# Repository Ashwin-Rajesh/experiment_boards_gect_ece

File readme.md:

# Working models

---

# Index
- [Working models](#working-models)
- [Index](#index)
- [Projects](#projects)
- [KiCad](#kicad)
  - [Introduction](#introduction)
  - [KiCad design flow](#kicad-design-flow)
    - [Creating the project](#creating-the-project)
    - [In eschema](#in-eschema)
    - [In PCBnew](#in-pcbnew)
    - [Other points](#other-points)
    - [Layout layers](#layout-layers)
  - [Design standards for the boards](#design-standards-for-the-boards)

---

# Projects

1) Series voltage regulator with feedback

---

# KiCad

## Introduction

KiCad is used for all schematic and board design. First, each board has a separate project. KiCad projects have 4 types of files 
- ```.pro```
  - Stores project related information
- ```.lib```
  - Libraries
- ```.sch```
  - Schematic file
  - Opened using ```Eeschema```
- ```.kicad_pcb```
  - PCB layout file
  - Opened using ```PCBnew```
- ```.net```
  - Netlist file
- ```.gbr```
  - Gerber files
  - Files used to define layers for fabrication
  - Opened using ```gerbview```

Software that are part of KiCad
- ```Eeschema```
  - Schematic editor and viewer
  - File extension : ```.sch```
- ```PCBnew```
  - Layout editor and viewer
  - File extension : ```.kicad_pcb```
- ```Gerbview```
  - Viewer for gerber files
  - File extension : ```.grbjob```

---

## KiCad design flow

### Creating the project
1) Create a project using ```File``` -> ```New``` -> ```Project```. 

### In eschema

1) Click on the ```.sch``` file to open schematic in eeschema
2) Draw the layout
    - Add components using ```Place symbol``` on the right pane or shortcut ```A```
    - Connect them using wires (Right pane : ```Place wire```, shortcut ```W```)
    - Place labels (Right pane : ```Place net label```, ```Place global label```)
    - Add text and stuff if you need it
3) Run ```Annotate schematic symbols``` on the top.
4) Perform DRC using ```Perform design rules check``` on the top.
5) Assign footprints to the symbols we have added using ```Assign PCB footprints to schematic symbols``` in the top.
6) Generate netlist using ```generate netlist``` button on the top.
7) Open PCBnew using ```run PCBnew to layout printed circuit board```

### In PCBnew

1) Run ```Update PCB from schematic``` to import the required footprints from the previous step
2) Arrange the components
     - Move using ```M```
     - Add filled zones using ```Add filled zones``` in the right pane
     - Add wires using ```Route tracks``` in the right pane 
       - Choose required layer in ```layers``` tab in right pane
       - If the layers tab is not visible, check ```show/hide layers manager toolbar```
     - Right click filled zones and ```fill``` to generate gaps
3) Add text and lines and stuff for layers
4) Define board outline using polygons or lines on the ```Edge.cuts``` layer

### Other points

- You can navigate easily between PCBnew and eeschema using buttons on the top
- Everytime you make a change in the schematic, it needs to be updated in the PCB. 
  - Run ```Update PCB from schematic``` in ```PCBnew``` when this is needed 
  - Change options as required
  - No need to generate netlist everytime

### Layout layers

- ```F.Cu``` : Front copper
- ```B.Cu``` : Back copper
- ```F.Silks``` : Front silkscreen
- ```B.Silks``` : Back silkscreen
- ```Edge.cuts``` : Edges of the PCB

---

## Design standards for the boards

- Height must be ```78mm```
- Length maximum ```155mm```
- Use connectors for ```2.54mm```

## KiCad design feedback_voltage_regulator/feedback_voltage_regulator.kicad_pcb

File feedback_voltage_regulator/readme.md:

# Feedback controlled voltage regulator

Linear series voltage regulator with feedback.

---

### Schematic

---

### PCB layout

Dimensions : ```135mm x 78mm```

---

### Gerber file 

---

### 3D view

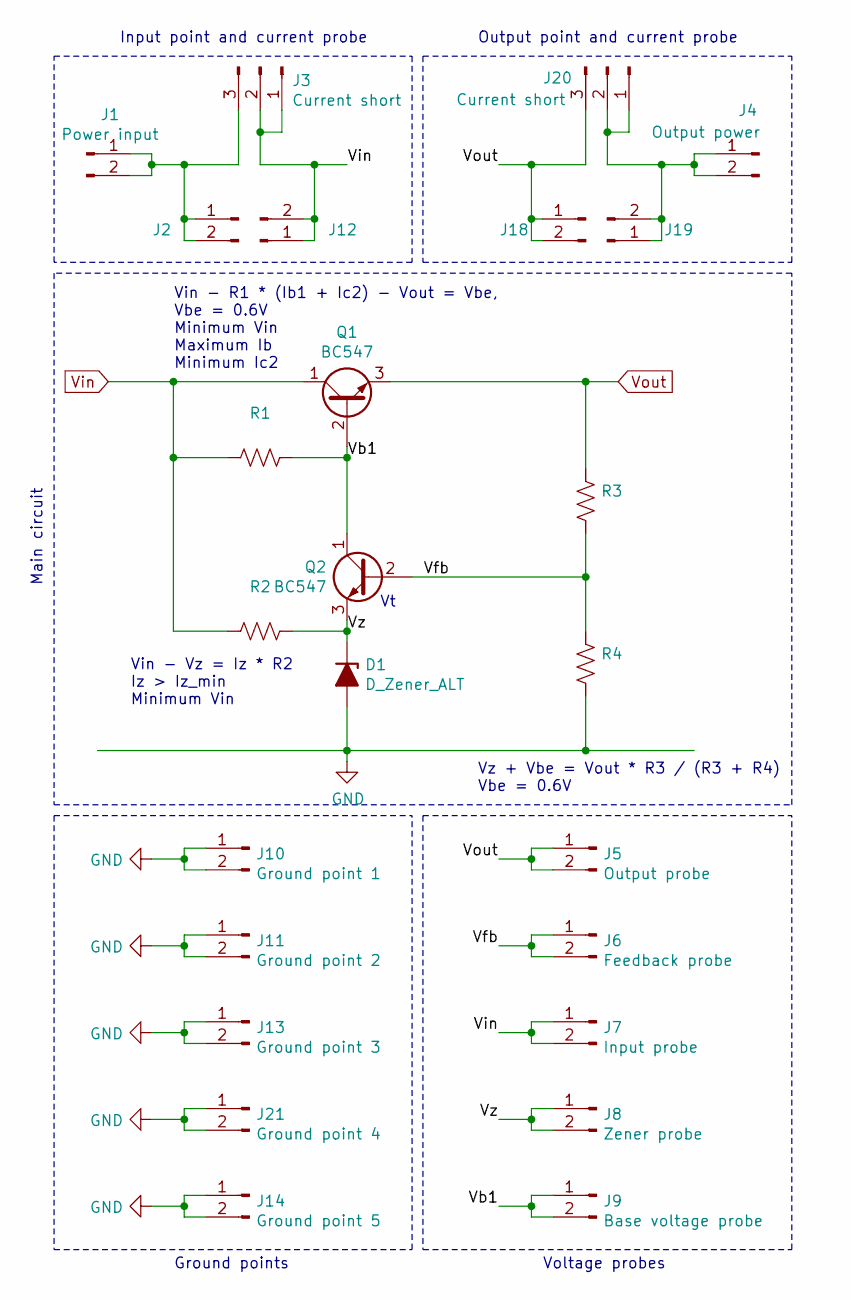
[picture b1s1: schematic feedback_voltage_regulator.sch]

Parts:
D1: D_Zener_ALT; D_DO-15_P15.24mm_Horizontal
J1: Power input; PinHeader_1x02_P2.54mm_Vertical
J2, J12, J18, J19: Input current probe; PinHeader_1x02_P2.54mm_Vertical
J3, J20: Current short; PinHeader_1x03_P2.54mm_Vertical
J4: Output power; PinHeader_1x02_P2.54mm_Vertical
J5: Output probe; PinHeader_1x02_P2.54mm_Vertical
J6: Feedback probe; PinHeader_1x02_P2.54mm_Vertical
J7: Input probe; PinHeader_1x02_P2.54mm_Vertical
J8: Zener probe; PinHeader_1x02_P2.54mm_Vertical
J9: Base voltage probe; PinHeader_1x02_P2.54mm_Vertical
J10: Ground point 1; PinHeader_1x02_P2.54mm_Vertical
J11: Ground point 2; PinHeader_1x02_P2.54mm_Vertical
J13: Ground point 3; PinHeader_1x02_P2.54mm_Vertical
J14: Ground point 5; PinHeader_1x02_P2.54mm_Vertical
J21: Ground point 4; PinHeader_1x02_P2.54mm_Vertical
Q1, Q2: BC547; TO-39-3
R1, R2, R3, R4: R_US; R_Axial_DIN0309_L9.0mm_D3.2mm_P15.24mm_Horizontal

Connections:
/Vb1: J9.1, J9.2, Q1.2 (B), Q2.1 (C), R1.1
/Vfb: J6.1, J6.2, Q2.2 (B), R3.2, R4.1
/Vz: D1.1 (K), J8.1, J8.2, Q2.3 (E), R2.1
GND: D1.2 (A), J10.1, J10.2, J11.1, J11.2, J13.1, J13.2, J14.1, J14.2, J21.1, J21.2, R4.2
unnamed: J1.1, J1.2, J2.1, J2.2, J3.3
unnamed: J4.1, J4.2, J19.1, J19.2, J20.1, J20.2
Vin: J3.1, J3.2, J7.1, J7.2, J12.1, J12.2, Q1.1 (C), R1.2, R2.2
Vout: J5.1, J5.2, J18.1, J18.2, J20.3, Q1.3 (E), R3.1

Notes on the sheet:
Vin - R1 * (Ib1 + Ic2) - Vout = Vbe, Vbe = 0.6V Minimum Vin Maximum Ib Minimum Ic2
Vin - Vz = Iz * R2 Iz > Iz_min Minimum Vin
Vz + Vbe = Vout * R3 / (R3 + R4) Vbe = 0.6V
Voltage probes
Ground points
Output point and current probe
Input point and current probe
Main circuit

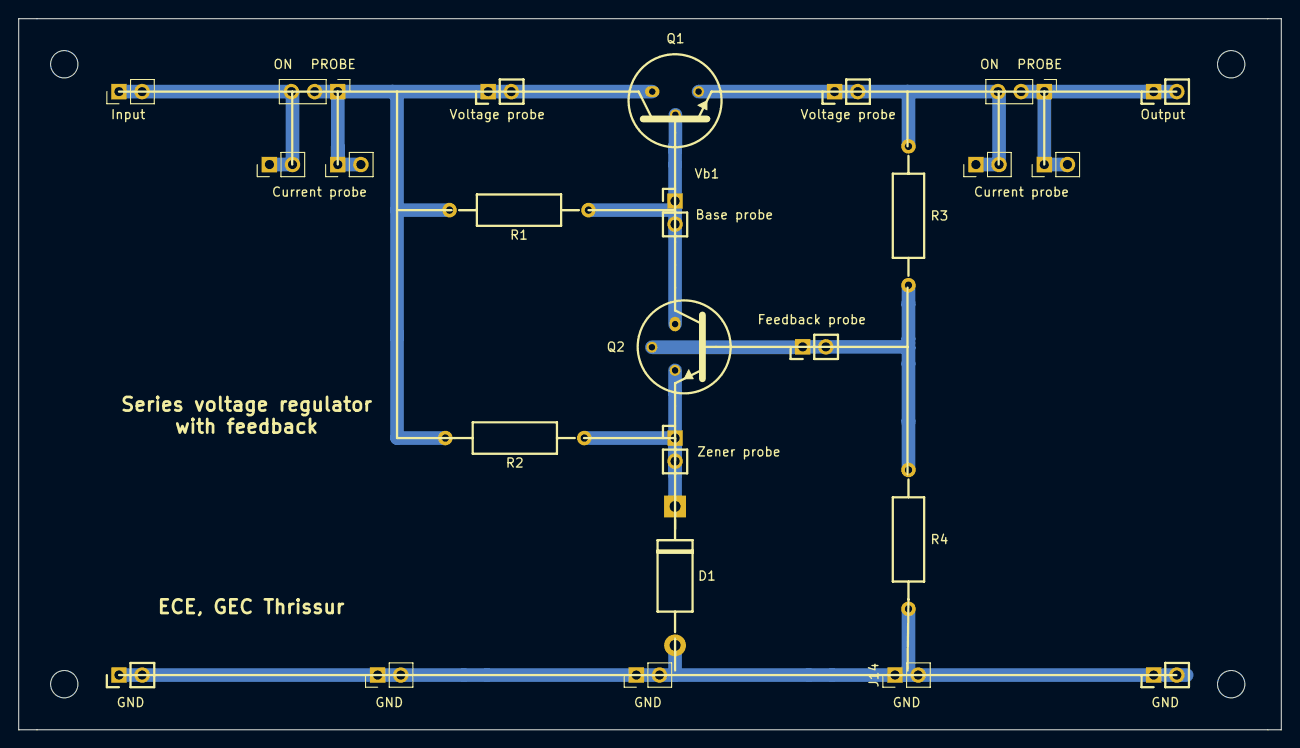
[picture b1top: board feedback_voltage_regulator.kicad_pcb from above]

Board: 2 copper layers, 138.5 x 78.0 mm, 25 parts (0 on the bottom side), 8 nets.

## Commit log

2021-11-26 Added feedback voltage regulator
2021-11-26 Moved screenshots to docs folder
2021-11-26 Minor changes
2021-11-26 Added 3d view
2021-11-26 Updated schematic symbols and size
